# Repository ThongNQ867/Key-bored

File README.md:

# Key-bored
This is a split keyboard that uses XIAO nRF52840 and MX switches with hotswap, LED and 3-D printed case.

This project is a Split wireless keyboard that run on 2 Xiao nRF52840 on each side. This keyboard runs on ZMM firmware and used MX switches. I made this project because split keyboards are very expensive and I think making one will help people have the similar experience with relatively lower price. Also, the parts like Xiao are reuseable for many projects, making it really cost effective. 

How to use:
- After print the PCBA from JLC PCB or order the parts and hand soldered them, solder the hotswap sockets, Xiao, JST pins into the pcb, and finally attach the swithces into the socket.
- Wire the Xiao with your computer and flash each of them with the firmware
Basicaly we got a working keyboard now.
- For the case, put the heat inserts in, lay the pcb on top and screw it with M3 (3mm) screws.

The assembled design should look like this

The PCB design:

Schematic (each side):

BOM:

## Bill of Materials (BOM)

| Name                         | Comment              | Footprint                              | JLCPCB Part #                  | Quantity | Links                                                                 | Price (Not include shipping) |
|------------------------------|----------------------|----------------------------------------|---------------------------------|----------|------------------------------------------------------------------------|-------------------------------|
| CR0805F88063G                | 806k                 | R_0805_2012Metric                      | C101872                        | 4        | https://jlcpcb.com/partdetail/LIZElec-CR0805F88063G/C101872           | Within PCB                    |
| 1N4148W diode                | 1N4148W              | D_SOD-123                              | C81598                         | 46       | https://jlcpcb.com/partdetail/ST_Semtech-1N4148W/C81598               | Within PCB                    |
|                              |                      | TestPoint_Pad_D2.0mm                   |                                 | 4        |                                                                        | Within PCB                    |
| PCB from JLCPCB              |                      |                                        |                                 | 1        |                                                                        | 35.71                         |
| Kalih hotswap sockets        |                      | SW_MX_HS_CPG151101S11_1u               | Not from JLC PCB               | 46       | https://www.aliexpress.us/item/3256809253442692.html                  | 12.17                         |
| XIAO nRF52840 SMD            |                      | modified-XIAO-nRF52840-SMD             | Not from JLC PCB               | 2        | https://www.aliexpress.us/item/3256806802639384.html                  | 17.96                         |
| SK6812MINI - E               | SK6812               | MX_SK6812MINI-E_REV                    | Hand solder, not from JLC PCB  | 46       | https://www.aliexpress.us/item/3256805061849599.html                  | 6.16                          |
| JST connector                |                      | JST_PH_S2B-PH-K_1x02_P2.00mm_Horizontal| Not from JLC PCB               | 2        | https://www.aliexpress.us/item/3256804769340392.html                  | 1.60                          |
| MX switches                  |                      |                                        | Not from JLC PCB               | 46       | https://www.aliexpress.us/item/3256805881801670.html                  | 8.05                          |
| Rechargeable LiPo battery    | 3.7V 100mAh          |                                        | Not from JLC PCB               | 2        | https://www.aliexpress.us/item/3256805604531299.html                  | 7.01                          |
| Heat inserts                 | M3x5x4               |                                        | Not from JLC PCB               |    10      | https://www.aliexpress.us/p/shoppingcart/index.html                   | 2.63                          |

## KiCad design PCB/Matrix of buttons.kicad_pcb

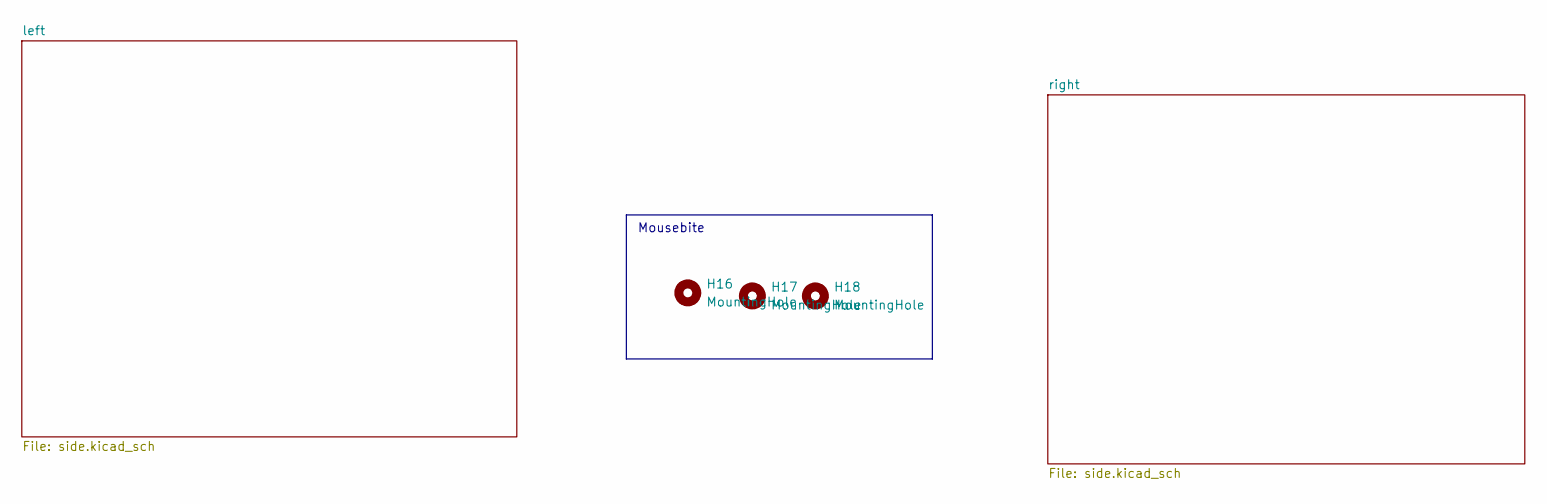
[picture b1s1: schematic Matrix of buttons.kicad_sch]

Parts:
H16, H17, H18: MountingHole; mouse-bite-5mm-slot

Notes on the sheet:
Mousebite

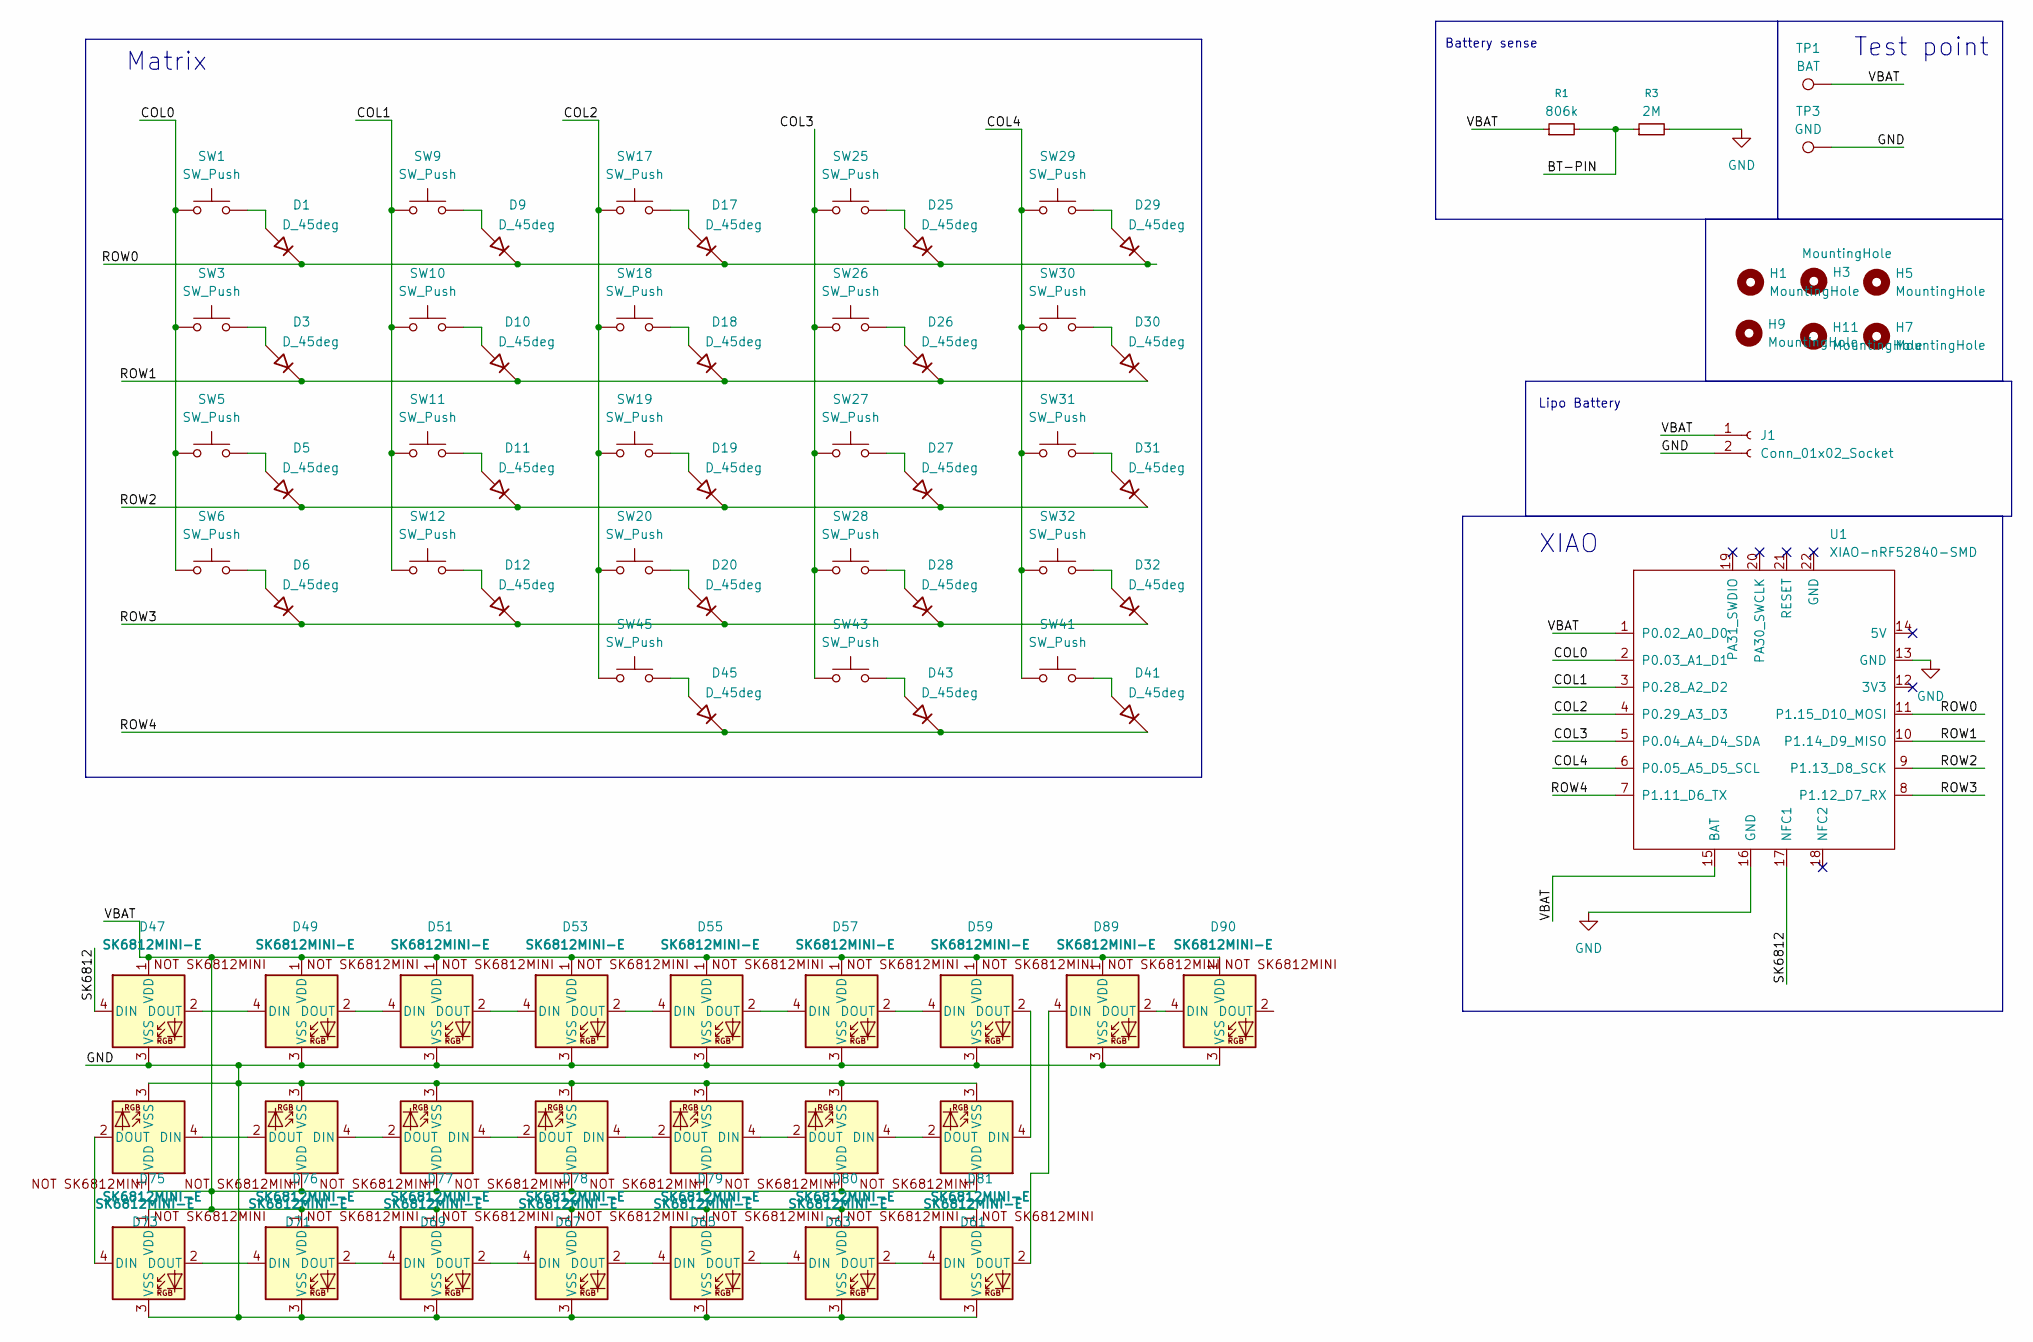
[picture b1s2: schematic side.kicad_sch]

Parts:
D1, D3, D5, D6, D9, D10, D11, D12, D17, D18, D19, D20, D25, D26, D27, D28, D29, D30, D31, D32, D41, D43, D45: D_45deg; D_SOD-123
D47, D49, D51, D53, D55, D57, D59, D61, D63, D65, D67, D69, D71, D73, D75, D76, D77, D78, D79, D80, D81, D89, D90: SK6812MINI-E; MX_SK6812MINI-E_REV
H1, H3, H5, H7, H9, H11: MountingHole; MountingHole_3mm
J1: Conn_01x02_Socket; JST_PH_S2B-PH-K_1x02_P2.00mm_Horizontal
R1: 806k; R_0805_2012Metric
R3: 2M; R_0805_2012Metric
SW1, SW3, SW5, SW6, SW9, SW10, SW11, SW12, SW17, SW18, SW19, SW20, SW25, SW26, SW27, SW28, SW29, SW30, SW31, SW32, SW41, SW43, SW45: SW_Push; SW_MX_HS_CPG151101S11_1u
TP1: BAT; TestPoint_Pad_D2.0mm
TP3: GND; TestPoint_Pad_D2.0mm
U1: XIAO-nRF52840-SMD; modified-XIAO-nRF52840-SMD

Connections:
/left/BT-PIN: R1.2, R3.1
/left/COL0: SW1.1, SW3.1, SW5.1, SW6.1, U1.2 (P0.03_A1_D1)
/left/COL1: SW9.1, SW10.1, SW11.1, SW12.1, U1.3 (P0.28_A2_D2)
/left/COL2: SW17.1, SW18.1, SW19.1, SW20.1, SW45.1, U1.4 (P0.29_A3_D3)
/left/COL3: SW25.1, SW26.1, SW27.1, SW28.1, SW43.1, U1.5 (P0.04_A4_D4_SDA)
/left/COL4: SW29.1, SW30.1, SW31.1, SW32.1, SW41.1, U1.6 (P0.05_A5_D5_SCL)
/left/ROW0: D1.1 (K), D9.1 (K), D17.1 (K), D25.1 (K), D29.1 (K), U1.11 (P1.15_D10_MOSI)
/left/ROW1: D3.1 (K), D10.1 (K), D18.1 (K), D26.1 (K), D30.1 (K), U1.10 (P1.14_D9_MISO)
/left/ROW2: D5.1 (K), D11.1 (K), D19.1 (K), D27.1 (K), D31.1 (K), U1.9 (P1.13_D8_SCK)
/left/ROW3: D6.1 (K), D12.1 (K), D20.1 (K), D28.1 (K), D32.1 (K), U1.8 (P1.12_D7_RX)
/left/ROW4: D41.1 (K), D43.1 (K), D45.1 (K), U1.7 (P1.11_D6_TX)
/left/SK6812: D47.4 (DIN), U1.17 (NFC1)
/left/VBAT: D47.1 (VDD), D49.1 (VDD), D51.1 (VDD), D53.1 (VDD), D55.1 (VDD), D57.1 (VDD), D59.1 (VDD), D61.1 (VDD), D63.1 (VDD), D65.1 (VDD), D67.1 (VDD), D69.1 (VDD), D71.1 (VDD), D73.1 (VDD), D75.1 (VDD), D76.1 (VDD), D77.1 (VDD), D78.1 (VDD), D79.1 (VDD), D80.1 (VDD), D81.1 (VDD), D89.1 (VDD), D90.1 (VDD), J1.1, R1.1, TP1.1, U1.1 (P0.02_A0_D0), U1.15 (BAT)
GND: D47.3 (VSS), D49.3 (VSS), D51.3 (VSS), D53.3 (VSS), D55.3 (VSS), D57.3 (VSS), D59.3 (VSS), D61.3 (VSS), D63.3 (VSS), D65.3 (VSS), D67.3 (VSS), D69.3 (VSS), D71.3 (VSS), D73.3 (VSS), D75.3 (VSS), D76.3 (VSS), D77.3 (VSS), D78.3 (VSS), D79.3 (VSS), D80.3 (VSS), D81.3 (VSS), D89.3 (VSS), D90.3 (VSS), J1.2, R3.2, TP3.1, U1.13 (GND), U1.16 (GND); also elsewhere on the board
unnamed: D1.2 (A), SW1.2
unnamed: D3.2 (A), SW3.2
unnamed: D5.2 (A), SW5.2
unnamed: D6.2 (A), SW6.2
unnamed: D9.2 (A), SW9.2
unnamed: D10.2 (A), SW10.2
unnamed: D11.2 (A), SW11.2
unnamed: D12.2 (A), SW12.2
unnamed: D17.2 (A), SW17.2
unnamed: D18.2 (A), SW18.2
unnamed: D19.2 (A), SW19.2
unnamed: D20.2 (A), SW20.2
unnamed: D25.2 (A), SW25.2
unnamed: D26.2 (A), SW26.2
unnamed: D27.2 (A), SW27.2
unnamed: D28.2 (A), SW28.2
unnamed: D29.2 (A), SW29.2
unnamed: D30.2 (A), SW30.2
unnamed: D31.2 (A), SW31.2
unnamed: D32.2 (A), SW32.2
unnamed: D41.2 (A), SW41.2
unnamed: D43.2 (A), SW43.2
unnamed: D45.2 (A), SW45.2
unnamed: D47.2 (DOUT), D49.4 (DIN)
unnamed: D49.2 (DOUT), D51.4 (DIN)
unnamed: D51.2 (DOUT), D53.4 (DIN)
unnamed: D53.2 (DOUT), D55.4 (DIN)
unnamed: D55.2 (DOUT), D57.4 (DIN)
unnamed: D57.2 (DOUT), D59.4 (DIN)
unnamed: D59.2 (DOUT), D61.4 (DIN)
unnamed: D61.2 (DOUT), D63.4 (DIN)
unnamed: D63.2 (DOUT), D65.4 (DIN)
unnamed: D65.2 (DOUT), D67.4 (DIN)
unnamed: D67.2 (DOUT), D69.4 (DIN)
unnamed: D69.2 (DOUT), D71.4 (DIN)
unnamed: D71.2 (DOUT), D73.4 (DIN)
unnamed: D73.2 (DOUT), D75.4 (DIN)
unnamed: D75.2 (DOUT), D76.4 (DIN)
unnamed: D76.2 (DOUT), D77.4 (DIN)
unnamed: D77.2 (DOUT), D78.4 (DIN)
unnamed: D78.2 (DOUT), D79.4 (DIN)
unnamed: D79.2 (DOUT), D80.4 (DIN)
unnamed: D80.2 (DOUT), D81.4 (DIN)
unnamed: D81.2 (DOUT), D89.4 (DIN)
unnamed: D89.2 (DOUT), D90.4 (DIN)

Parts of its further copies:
D2, D4, D7, D8, D13, D14, D15, D16, D21, D22, D23, D24, D33, D34, D35, D36, D37, D38, D39, D40, D42, D44, D46: D_45deg; D_SOD-123
D48, D50, D52, D54, D56, D58, D60, D62, D64, D66, D68, D70, D72, D74, D82, D83, D84, D85, D86, D87, D88, D91, D92: SK6812MINI-E; MX_SK6812MINI-E_REV
H2, H4, H6, H8, H10, H12: MountingHole; MountingHole_3mm
J2: Conn_01x02_Socket; JST_PH_S2B-PH-K_1x02_P2.00mm_Horizontal
R2: 806k; R_0805_2012Metric
R4: 2M; R_0805_2012Metric
SW2, SW4, SW7, SW8, SW13, SW14, SW15, SW16, SW21, SW22, SW23, SW24, SW33, SW34, SW35, SW36, SW37, SW38, SW39, SW40, SW42, SW44, SW46: SW_Push; SW_MX_HS_CPG151101S11_1u
TP2: BAT; TestPoint_Pad_D2.0mm
TP4: GND; TestPoint_Pad_D2.0mm
U2: XIAO-nRF52840-SMD; modified-XIAO-nRF52840-SMD

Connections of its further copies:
/right/BT-PIN: R2.2, R4.1
/right/COL0: SW2.1, SW4.1, SW7.1, SW8.1, U2.2 (P0.03_A1_D1)
/right/COL1: SW13.1, SW14.1, SW15.1, SW16.1, U2.3 (P0.28_A2_D2)
/right/COL2: SW21.1, SW22.1, SW23.1, SW24.1, SW46.1, U2.4 (P0.29_A3_D3)
/right/COL3: SW33.1, SW34.1, SW35.1, SW36.1, SW44.1, U2.5 (P0.04_A4_D4_SDA)
/right/COL4: SW37.1, SW38.1, SW39.1, SW40.1, SW42.1, U2.6 (P0.05_A5_D5_SCL)
/right/ROW0: D2.1 (K), D13.1 (K), D21.1 (K), D33.1 (K), D37.1 (K), U2.11 (P1.15_D10_MOSI)
/right/ROW1: D4.1 (K), D14.1 (K), D22.1 (K), D34.1 (K), D38.1 (K), U2.10 (P1.14_D9_MISO)
/right/ROW2: D7.1 (K), D15.1 (K), D23.1 (K), D35.1 (K), D39.1 (K), U2.9 (P1.13_D8_SCK)
/right/ROW3: D8.1 (K), D16.1 (K), D24.1 (K), D36.1 (K), D40.1 (K), U2.8 (P1.12_D7_RX)
/right/ROW4: D42.1 (K), D44.1 (K), D46.1 (K), U2.7 (P1.11_D6_TX)
/right/SK6812: D48.4 (DIN), U2.17 (NFC1)
/right/VBAT: D48.1 (VDD), D50.1 (VDD), D52.1 (VDD), D54.1 (VDD), D56.1 (VDD), D58.1 (VDD), D60.1 (VDD), D62.1 (VDD), D64.1 (VDD), D66.1 (VDD), D68.1 (VDD), D70.1 (VDD), D72.1 (VDD), D74.1 (VDD), D82.1 (VDD), D83.1 (VDD), D84.1 (VDD), D85.1 (VDD), D86.1 (VDD), D87.1 (VDD), D88.1 (VDD), D91.1 (VDD), D92.1 (VDD), J2.1, R2.1, TP2.1, U2.1 (P0.02_A0_D0), U2.15 (BAT)
GND: D48.3 (VSS), D50.3 (VSS), D52.3 (VSS), D54.3 (VSS), D56.3 (VSS), D58.3 (VSS), D60.3 (VSS), D62.3 (VSS), D64.3 (VSS), D66.3 (VSS), D68.3 (VSS), D70.3 (VSS), D72.3 (VSS), D74.3 (VSS), D82.3 (VSS), D83.3 (VSS), D84.3 (VSS), D85.3 (VSS), D86.3 (VSS), D87.3 (VSS), D88.3 (VSS), D91.3 (VSS), D92.3 (VSS), J2.2, R4.2, TP4.1, U2.13 (GND), U2.16 (GND); also elsewhere on the board
unnamed: D2.2 (A), SW2.2
unnamed: D4.2 (A), SW4.2
unnamed: D7.2 (A), SW7.2
unnamed: D8.2 (A), SW8.2
unnamed: D13.2 (A), SW13.2
unnamed: D14.2 (A), SW14.2
unnamed: D15.2 (A), SW15.2
unnamed: D16.2 (A), SW16.2
unnamed: D21.2 (A), SW21.2
unnamed: D22.2 (A), SW22.2
unnamed: D23.2 (A), SW23.2
unnamed: D24.2 (A), SW24.2
unnamed: D33.2 (A), SW33.2
unnamed: D34.2 (A), SW34.2
unnamed: D35.2 (A), SW35.2
unnamed: D36.2 (A), SW36.2
unnamed: D37.2 (A), SW37.2
unnamed: D38.2 (A), SW38.2
unnamed: D39.2 (A), SW39.2
unnamed: D40.2 (A), SW40.2
unnamed: D42.2 (A), SW42.2
unnamed: D44.2 (A), SW44.2
unnamed: D46.2 (A), SW46.2
unnamed: D48.2 (DOUT), D50.4 (DIN)
unnamed: D50.2 (DOUT), D52.4 (DIN)
unnamed: D52.2 (DOUT), D54.4 (DIN)
unnamed: D54.2 (DOUT), D56.4 (DIN)
unnamed: D56.2 (DOUT), D58.4 (DIN)
unnamed: D58.2 (DOUT), D60.4 (DIN)
unnamed: D60.2 (DOUT), D62.4 (DIN)
unnamed: D62.2 (DOUT), D64.4 (DIN)
unnamed: D64.2 (DOUT), D66.4 (DIN)
unnamed: D66.2 (DOUT), D68.4 (DIN)
unnamed: D68.2 (DOUT), D70.4 (DIN)
unnamed: D70.2 (DOUT), D72.4 (DIN)
unnamed: D72.2 (DOUT), D74.4 (DIN)
unnamed: D74.2 (DOUT), D82.4 (DIN)
unnamed: D82.2 (DOUT), D83.4 (DIN)
unnamed: D83.2 (DOUT), D84.4 (DIN)
unnamed: D84.2 (DOUT), D85.4 (DIN)
unnamed: D85.2 (DOUT), D86.4 (DIN)
unnamed: D86.2 (DOUT), D87.4 (DIN)
unnamed: D87.2 (DOUT), D88.4 (DIN)
unnamed: D88.2 (DOUT), D91.4 (DIN)
unnamed: D91.2 (DOUT), D92.4 (DIN)

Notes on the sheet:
Battery sense
XIAO
Matrix
Lipo Battery
Test point

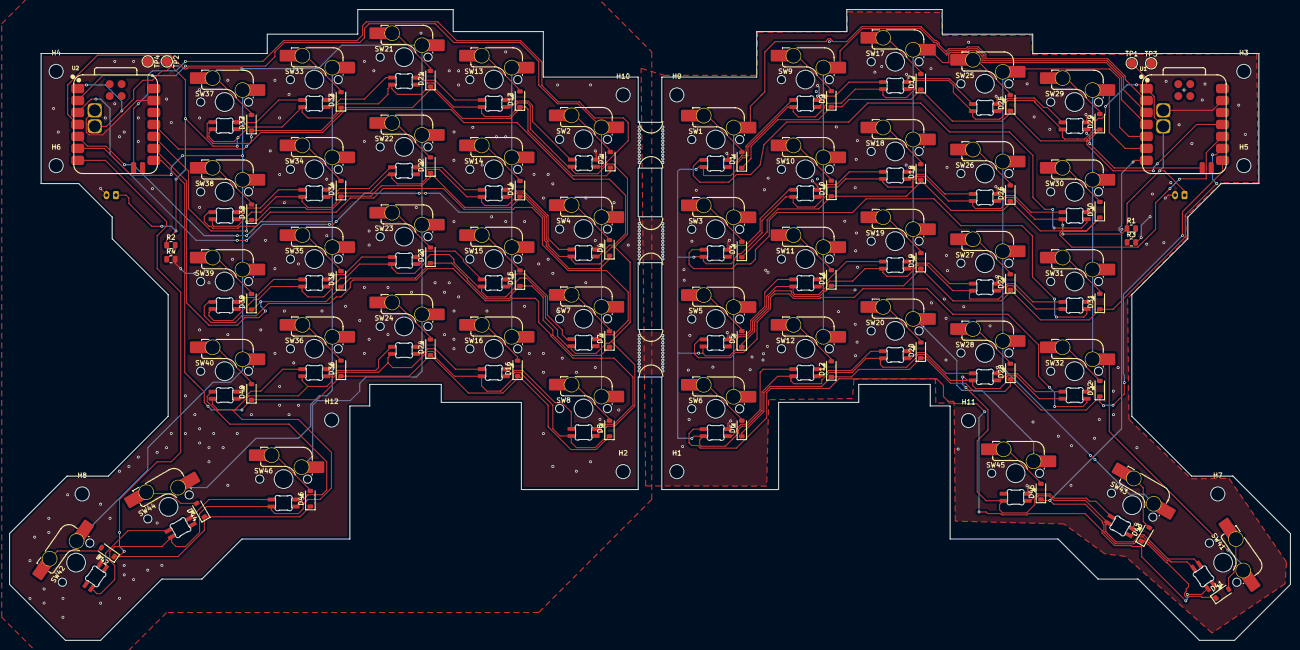
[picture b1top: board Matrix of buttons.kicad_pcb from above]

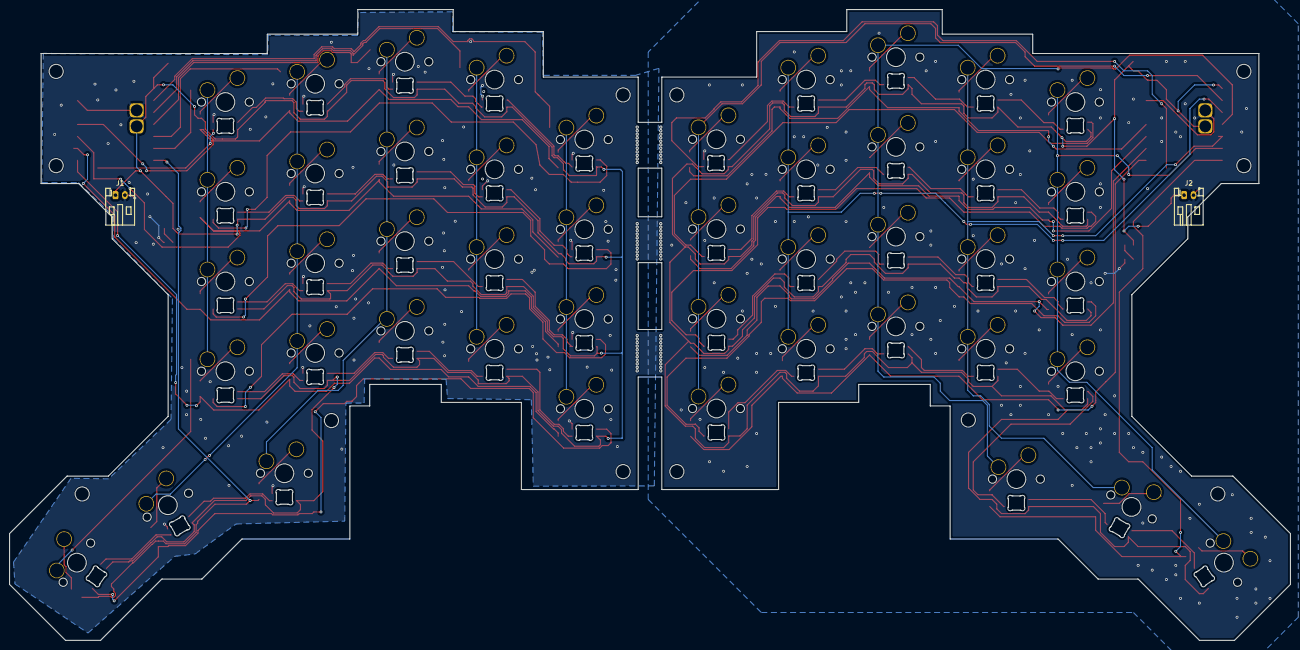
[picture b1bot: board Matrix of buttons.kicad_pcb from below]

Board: 2 copper layers, 271.9 x 133.9 mm, 165 parts (48 on the bottom side), 117 nets.

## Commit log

2026-03-18 bom to csv
2026-03-18 add CAD files and PCB files
2026-03-18 organize image
2026-03-18 images fix
2026-03-18 image fix
